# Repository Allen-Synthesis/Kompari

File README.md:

***
# Kompari
### A comparator module for Eurorack
  
***
### Features:
- 2 ±12V inputs, each with attenuverter
- Unipolar/Bipolar output switch
- 1 ±10V output, with attenuverter

Plug any CV or audio source into one of the two inputs, and it will be compared against the other.  

The output will be high (+10V) if input A is greater than input B.  

The output will be low (-10V if set to bipolar, 0V if set to unipolar) if input B is greater than input A.  

Both inputs have an attenuverter, and are both normalled to +12V, so with only one input, the value of input B can be controlled simply using the attenuverter as a ±10V voltage source.  
***

***
### Easy to DIY
The module has fairly few components, and is entirely through hole. It is also 'free hardware' so you can access all the design files in this repo, and check out the [Interactive Bill of Materials here!](https://htmlpreview.github.io/?https://raw.githubusercontent.com/Allen-Synthesis/Kompari/main/kicad/bom/ibom.html)

***
### Patch Examples

#### PWM
While the concept may seem simple, the versatility of a comparator in Eurorack is far reaching.  
For example, feeding a triangle wave input to input A will result in a square wave output of the same wave, and input B (or simply the attenuverter normalled to +12) will act as PWM to that square wave. Plug the original triangle and this new PWM square wave into a crossfader/mixer and you now have a pretty modulatable waveshaper.  
  
#### Compressor
Another more complex case would be to run an audio source through an envelope follower, then into input A. Use input B to set a maximum voltage (volume), and when the volume of the audio (envelope follower voltage) goes above this voltage, the Kompari output should trigger an envelope generator which has a negative effect on the volume of a VCA on the original audio. You now have a slightly roundabout, but fully fledged compressor! The envelope generator's attack and decay controls are the response of the compressor, the VCA's unaltered input voltage (before subtracting the envelope) is the makeup gain, and the Kompari's input B is the threshold.  
  
As you can see, it's easy to get carried away with using a comparator module such as the Kompari, and the patches you can make are only limited by your imagination!

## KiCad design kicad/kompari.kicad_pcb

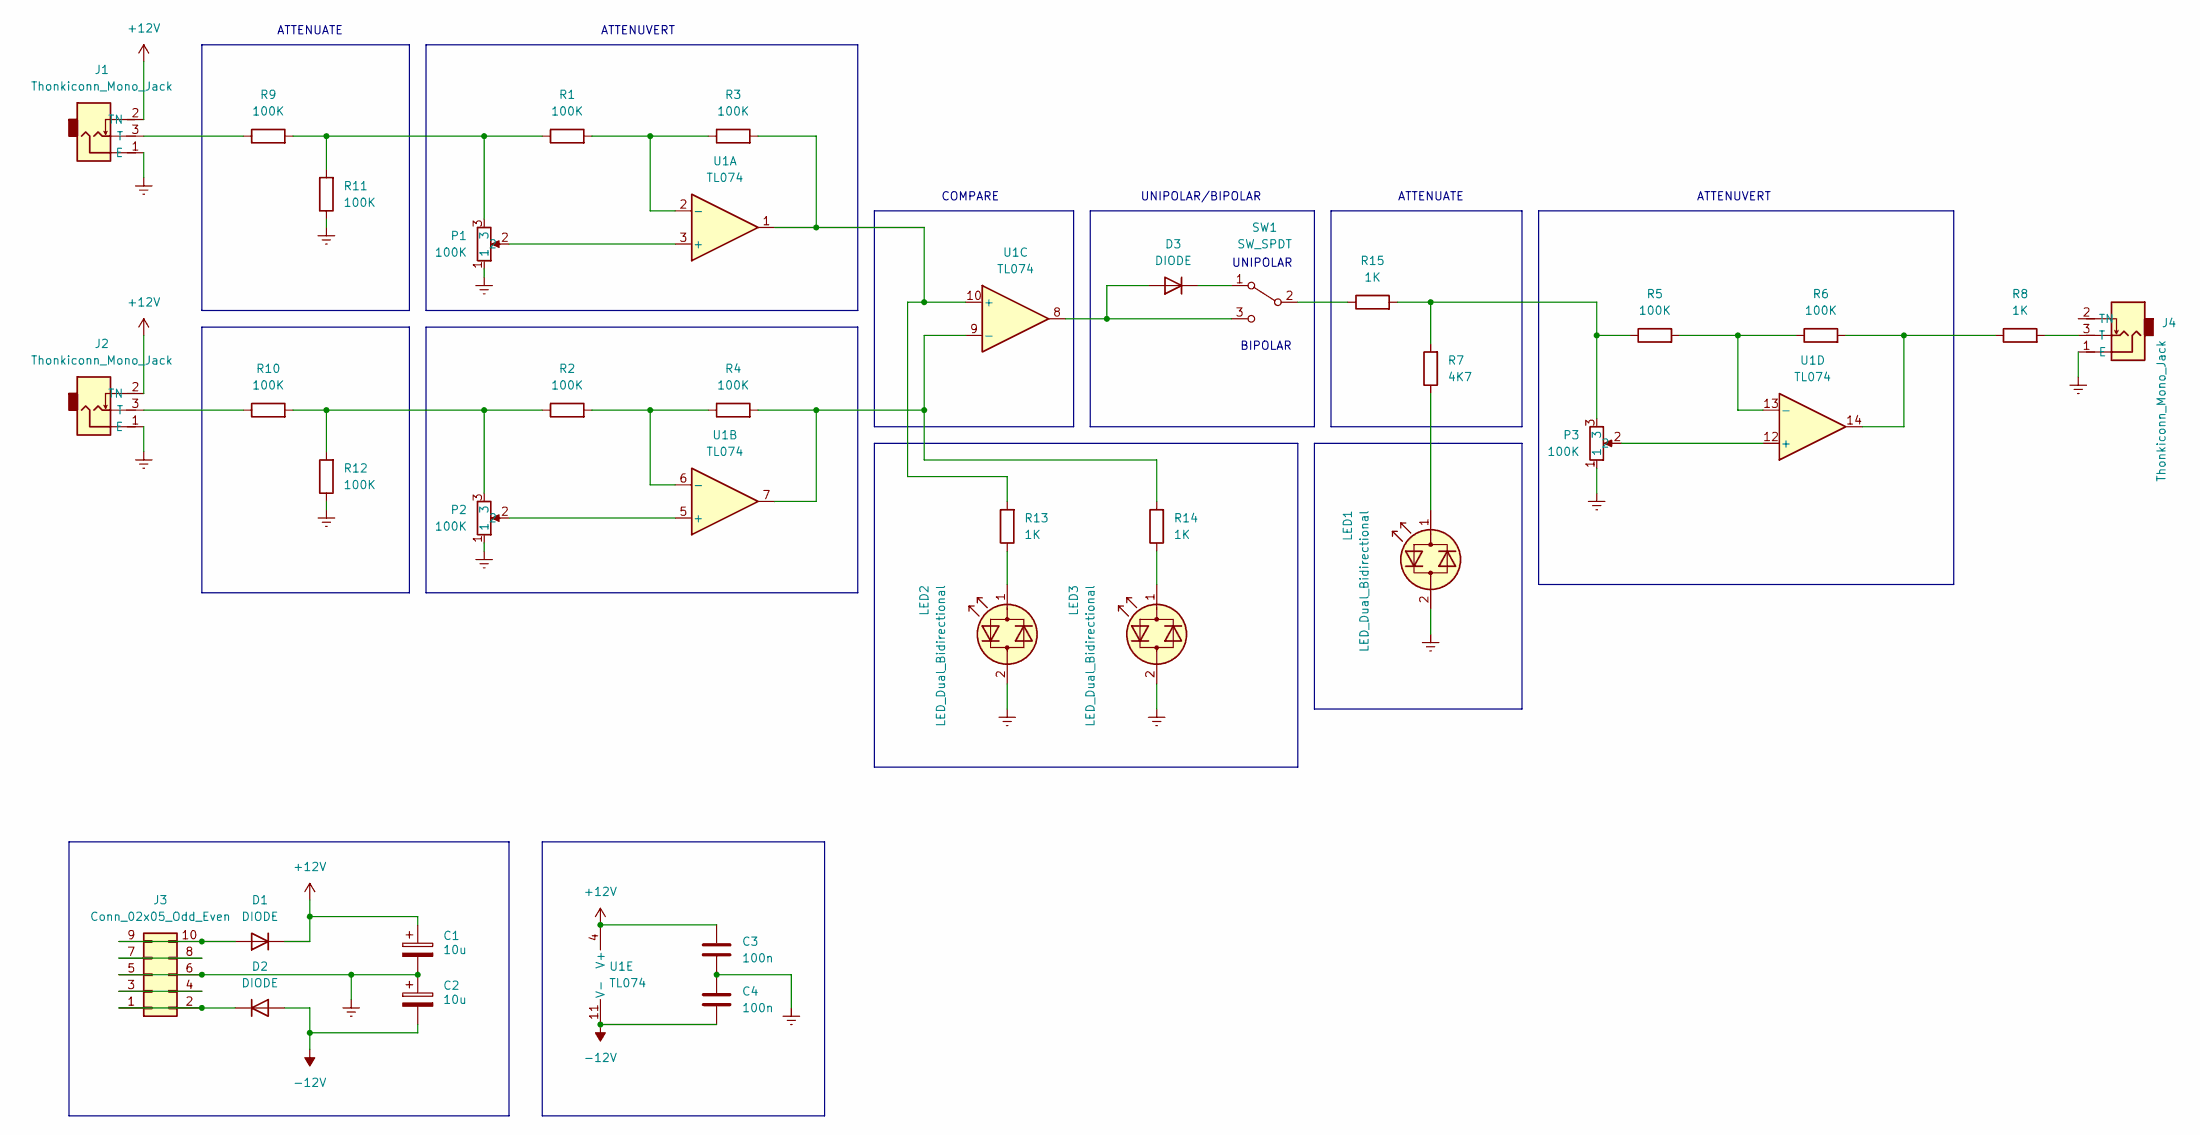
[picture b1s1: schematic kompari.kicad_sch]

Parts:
C1, C2: 10u; Capacitor Small Polarised
C3, C4: 100n; Capacitor Small Non-Polarised
D1, D2, D3: DIODE; Schottky Diode
J1, J2, J4: Thonkiconn_Mono_Jack; Thonkiconn Mono Jack
J3: Conn_02x05_Odd_Even; Eurorack Power Header
LED1, LED2, LED3: LED_Dual_Bidirectional; LED 3mm
P1, P2, P3: 100K; Potentiometer 9mm Vertical Linear Centred
R1, R2, R3, R4, R5, R6, R9, R10, R11, R12: 100K; Resistor 0.25W Through-Hole
R7: 4K7; Resistor 0.25W Through-Hole
R8, R13, R14, R15: 1K; Resistor 0.25W Through-Hole
SW1: SW_SPDT; Sub-Miniature Toggle Switch SPDT
U1: TL074; DIP-14 IC Socket

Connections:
+12V: C1.1, C3.1, D1.2 (K), J1.2 (TN), J2.2 (TN), U1.4 (V+)
-12V: C2.2, C4.2, D2.1 (A), U1.11 (V-)
Earth: C1.2, C2.1, C3.2, C4.1, J1.1 (E), J2.1 (E), J3.5, J3.6, J4.1 (E), LED1.2 (AK), LED2.2 (AK), LED3.2 (AK), P1.1, P2.1, P3.1, R11.1, R12.1
unnamed: D1.1 (A), J3.9, J3.10
unnamed: D2.2 (K), J3.1, J3.2
unnamed: D3.1 (A), SW1.3 (C), U1.8
unnamed: D3.2 (K), SW1.1 (A)
unnamed: J1.3 (T), R9.1
unnamed: J2.3 (T), R10.1
unnamed: J3.3, J3.4
unnamed: J3.7, J3.8
unnamed: J4.3 (T), R8.2
unnamed: LED1.1 (KA), R7.1
unnamed: LED2.1 (KA), R13.1
unnamed: LED3.1 (KA), R14.1
unnamed: P1.2, U1.3 (+)
unnamed: P1.3, R1.1, R9.2, R11.2
unnamed: P2.2, U1.5 (+)
unnamed: P2.3, R2.1, R10.2, R12.2
unnamed: P3.2, U1.12 (+)
unnamed: P3.3, R5.1, R7.2, R15.2
unnamed: R1.2, R3.1, U1.2 (-)
unnamed: R2.2, R4.1, U1.6 (-)
unnamed: R5.2, R6.1, U1.13 (-)
unnamed: R6.2, R8.1, U1.14
unnamed: R3.2, R13.2, U1.1, U1.10 (+)
unnamed: R4.2, R14.2, U1.7, U1.9 (-)
unnamed: R15.1, SW1.2 (B)

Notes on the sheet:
COMPARE
ATTENUATE
ATTENUVERT
UNIPOLAR
BIPOLAR
UNIPOLAR/BIPOLAR

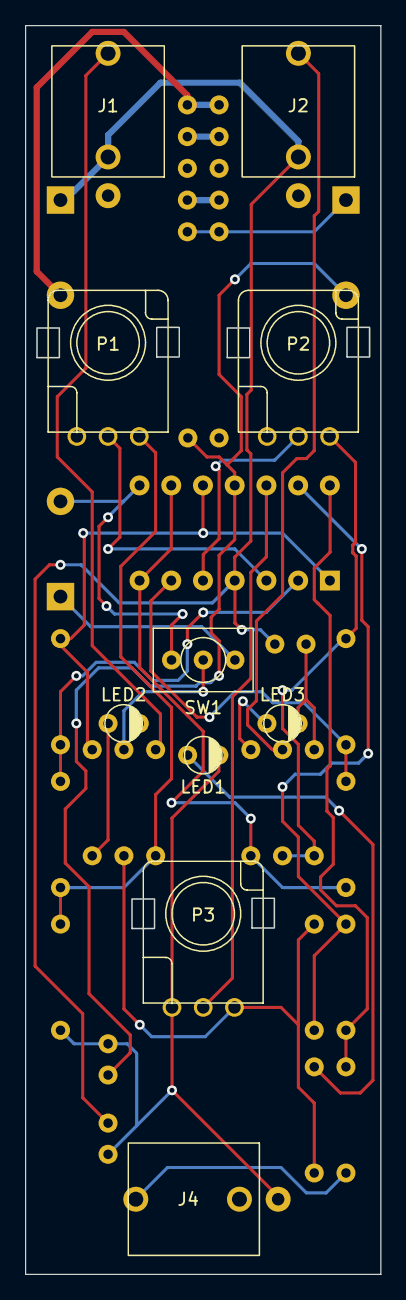
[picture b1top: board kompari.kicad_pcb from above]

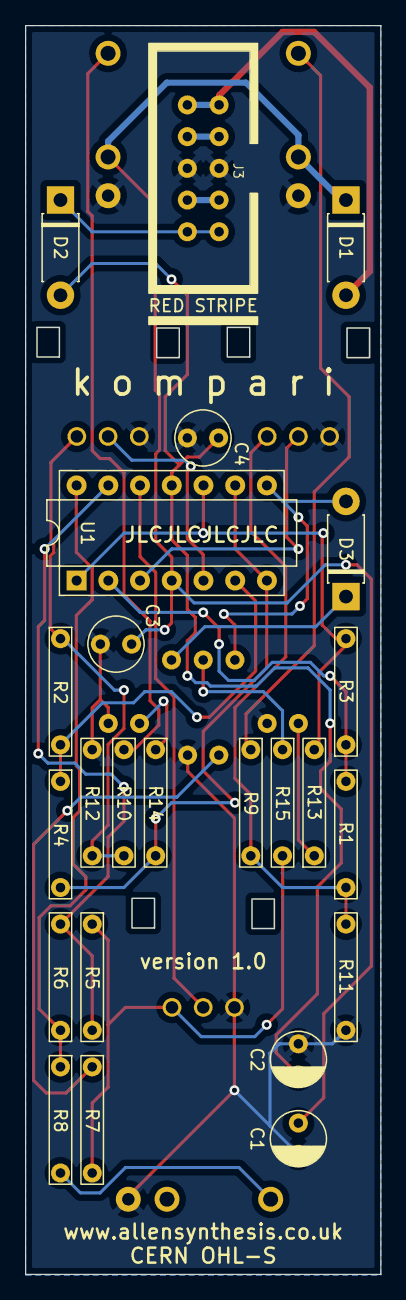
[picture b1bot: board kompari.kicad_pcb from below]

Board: 2 copper layers, 28.4 x 100.0 mm, 34 parts (24 on the bottom side), 28 nets.

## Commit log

2022-09-20 kicad save
2022-09-27 create user manual
2022-09-27 flow chart save
2022-09-27 Add BOM
2022-09-27 Add line breaks
2022-10-17 Save KiCad, create panel alternatives
2022-10-17 move experimental panels to folder
2022-10-17 Optimise PCB trace spacing, fix switch
    The switch was previously the wrong way round, so left would be bipolar when it should be left for unipolar. This has been fixed as well as general increasing of spacing between traces
2022-10-19 Add version number to PCB
    Add version number 1.0 to PCB
    Rotate C1 and C2 to not cover up website silkscreen
    Export Gerbers
2022-10-19 Update BOM link
2022-10-19 wording
2022-10-19 PCB improvements
    trace spacing
    wider traces for unprotected power lines
    potentiometer lug holes widened
    regenerate gerbers + bom
2022-10-19 add images
2023-08-15 save
2023-08-15 add black kicad panel
2023-09-01 add black panel
2023-09-01 clean up
2023-09-01 add panel gerber

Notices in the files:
kicad/kompari.kicad_pcb:
CERN OHL-S
